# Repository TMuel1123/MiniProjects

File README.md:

MiniProjects
============

This repository contains various mini projects where it would be to much to make a own repository for each project.

ATtiny85Minimal
-------------------------

This board was just a test of the order peocedure at OSH Park. It is a simple board which contains an ATtiny85 a button and a LED.

<pre>
// ATMEL ATTINY45 / ARDUINO
//
//                          +-\/-+
// (Reset) Ain0 (D 5) PB5  1|    |8  Vcc
//         Ain3 (D 3) PB3  2|    |7  PB2 (D 2) Ain1 (SCK)
//         Ain2 (D 4) PB4  3|    |6  PB1 (D 1) pwm1 (MISO)
//                    GND  4|    |5  PB0 (D 0) pwm0 (MOSI) INT0
//                          +----+
</pre>

* Bread board friendly
* Push button is connected to D0 which is INT0
* Has a LED connected to D1 which is a PWM output
* The gerber files in the zip file ./ATtiny85Minimal/Gerber+brd/ATtiny85Minimal.zip can be directly uploaded to OSHPark.com to order it.

MegaMiniProto
-------------------------

This is a shield for the last third of the Arduino Mega2560.

* It covers the pins 14-53 and A8-A15. These pins include USART 1-3 (14-19), I2C (20,21), PWM (44-46) and SPI (50-53).
* It still fits onto the Arduino Mega2560 if a normal shield ia connected to the Arduino Mega.
* The gerber files in the zip file ./Gerber+brd/MegaMiniProto.zip can be directly uploaded to OSHPark.com to order it.

3x_74HC595
-------------------------

This board contains three 74HC595 shift registers

* Bread board friendly
* the boards can be chained together
* The gerber files in the zip file ./3x_74HC595/Gerbers/3x_74HC595.zip can be directly uploaded to OSHPark.com to order it.

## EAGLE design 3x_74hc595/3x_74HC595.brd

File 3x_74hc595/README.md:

3x 74HC595
============

This board contains three 74HC595 shift registers

* Bread board friendly
* the boards can be chained together
* The gerber files in the zip file ./3x_74HC595/Gerbers/3x_74HC595.zip can be directly uploaded to OSHPark.com to order it.

Revision 1.1
------------
* Rounded edges of the board outline
* Added labels for the IO

Revision 1.2
------------
* Moved the OUT connector for better daisy chaining

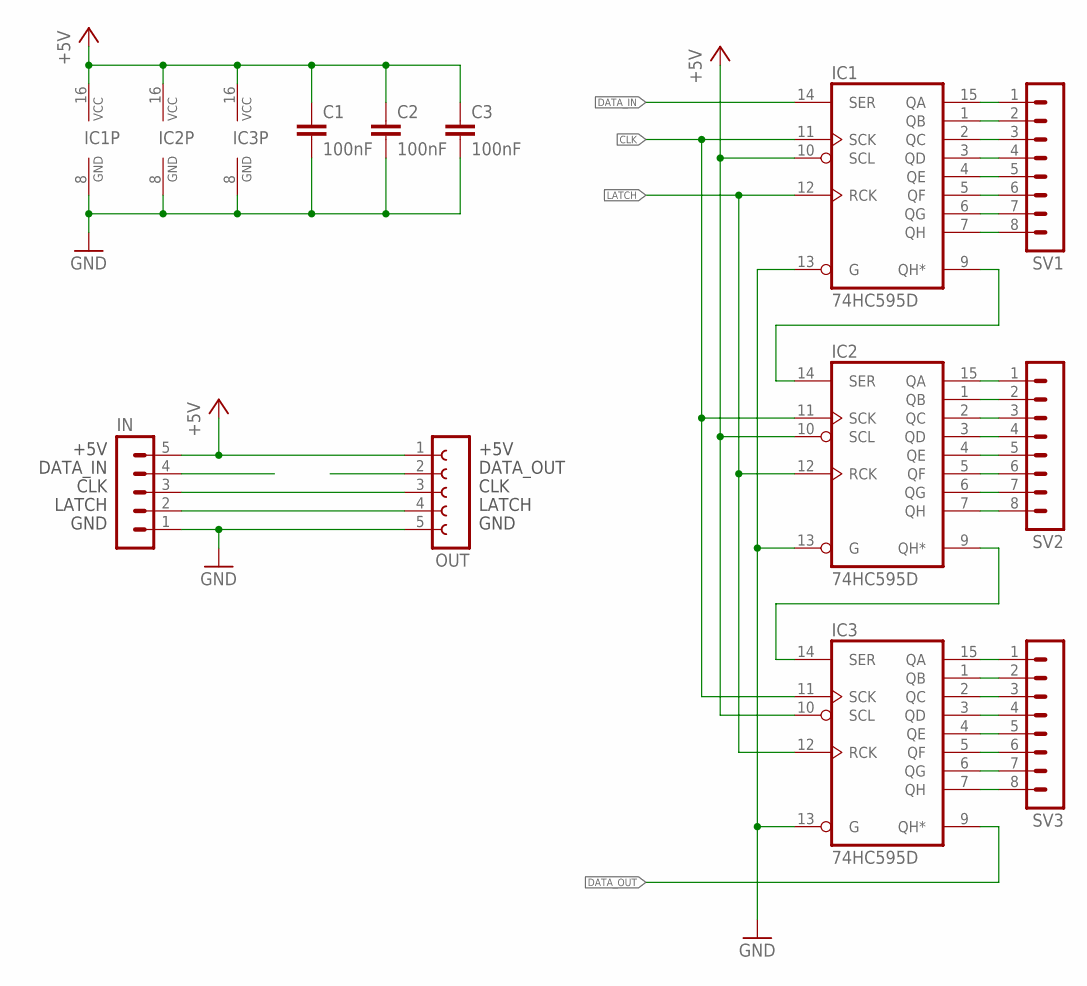
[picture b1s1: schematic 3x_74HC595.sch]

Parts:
C1, C2, C3: 100nF; C1206
IC1, IC2, IC3: 74HC595D; SO16
IN: MA05-1W
OUT: FE05W
SV1, SV2, SV3: MA08-1W

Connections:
1QA: IC1.15 (QA), SV1.1
1QB: IC1.1 (QB), SV1.2
1QC: IC1.2 (QC), SV1.3
1QD: IC1.3 (QD), SV1.4
1QE: IC1.4 (QE), SV1.5
1QF: IC1.5 (QF), SV1.6
1QG: IC1.6 (QG), SV1.7
1QH: IC1.7 (QH), SV1.8
1SHIFTOUT: IC1.9 (QH*), IC2.14 (SER)
2QA: IC2.15 (QA), SV2.1
2QB: IC2.1 (QB), SV2.2
2QC: IC2.2 (QC), SV2.3
2QD: IC2.3 (QD), SV2.4
2QE: IC2.4 (QE), SV2.5
2QF: IC2.5 (QF), SV2.6
2QG: IC2.6 (QG), SV2.7
2QH: IC2.7 (QH), SV2.8
2SHIFTOUT: IC2.9 (QH*), IC3.14 (SER)
3QA: IC3.15 (QA), SV3.1
3QB: IC3.1 (QB), SV3.2
3QC: IC3.2 (QC), SV3.3
3QD: IC3.3 (QD), SV3.4
3QE: IC3.4 (QE), SV3.5
3QF: IC3.5 (QF), SV3.6
3QG: IC3.6 (QG), SV3.7
3QH: IC3.7 (QH), SV3.8
+5V: C1.1, C2.1, C3.1, IC1.10 (SCL), IC1.16 (VCC), IC2.10 (SCL), IC2.16 (VCC), IC3.10 (SCL), IC3.16 (VCC), IN.5, OUT.1
CLK: IC1.11 (SCK), IC2.11 (SCK), IC3.11 (SCK), IN.3, OUT.3
DATA_IN: IC1.14 (SER), IN.4
DATA_OUT: IC3.9 (QH*), OUT.2
GND: C1.2, C2.2, C3.2, IC1.8 (GND), IC1.13 (G), IC2.8 (GND), IC2.13 (G), IC3.8 (GND), IC3.13 (G), IN.1, OUT.5
LATCH: IC1.12 (RCK), IC2.12 (RCK), IC3.12 (RCK), IN.2, OUT.4

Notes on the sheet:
+5V
DATA_IN
CLK
LATCH
GND
DATA_OUT

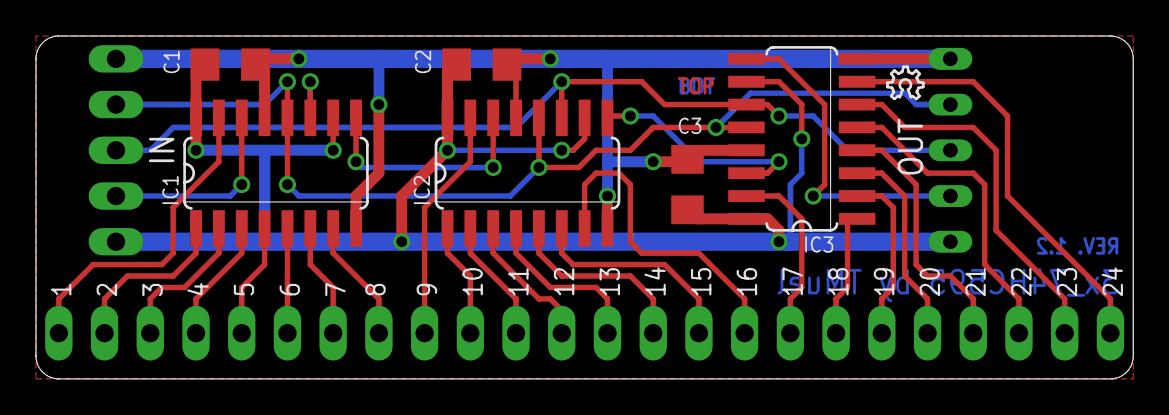
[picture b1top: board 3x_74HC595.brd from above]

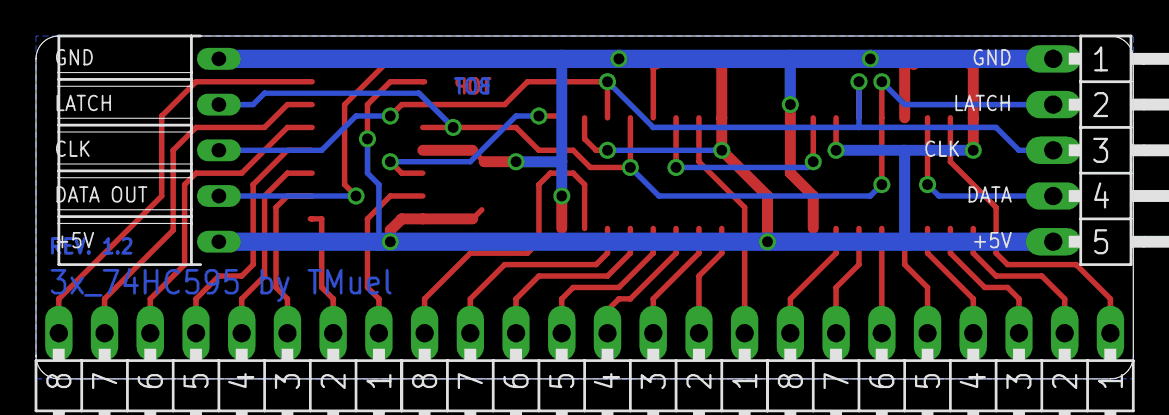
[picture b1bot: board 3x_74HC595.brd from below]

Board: 2 copper layers, 61.0 x 19.1 mm, 12 parts (5 on the bottom side), 32 nets.

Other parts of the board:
U$1: OSHW_6X70_NOTEXT

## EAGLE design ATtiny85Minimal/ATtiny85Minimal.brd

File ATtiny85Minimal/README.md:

ATtiny85Minimal
============

This board was just a test of the order peocedure at OSH Park. It is a simple board which contains an ATtiny85 a button and a LED.

<pre>
// ATMEL ATTINY45 / ARDUINO
//
//                          +-\/-+
// (Reset) Ain0 (D 5) PB5  1|    |8  Vcc
//         Ain3 (D 3) PB3  2|    |7  PB2 (D 2) Ain1 (SCK)
//         Ain2 (D 4) PB4  3|    |6  PB1 (D 1) pwm1 (MISO)
//                    GND  4|    |5  PB0 (D 0) pwm0 (MOSI) INT0
//                          +----+
</pre>

* Bread board friendly
* Push button is connected to D0 which is INT0
* Has a LED connected to D1 which is a PWM output
* The gerber files in the zip file ./ATtiny85Minimal/Gerber+brd_REV_1.0/ATtiny85Minimal.zip can be directly uploaded to OSHPark.com to order it.

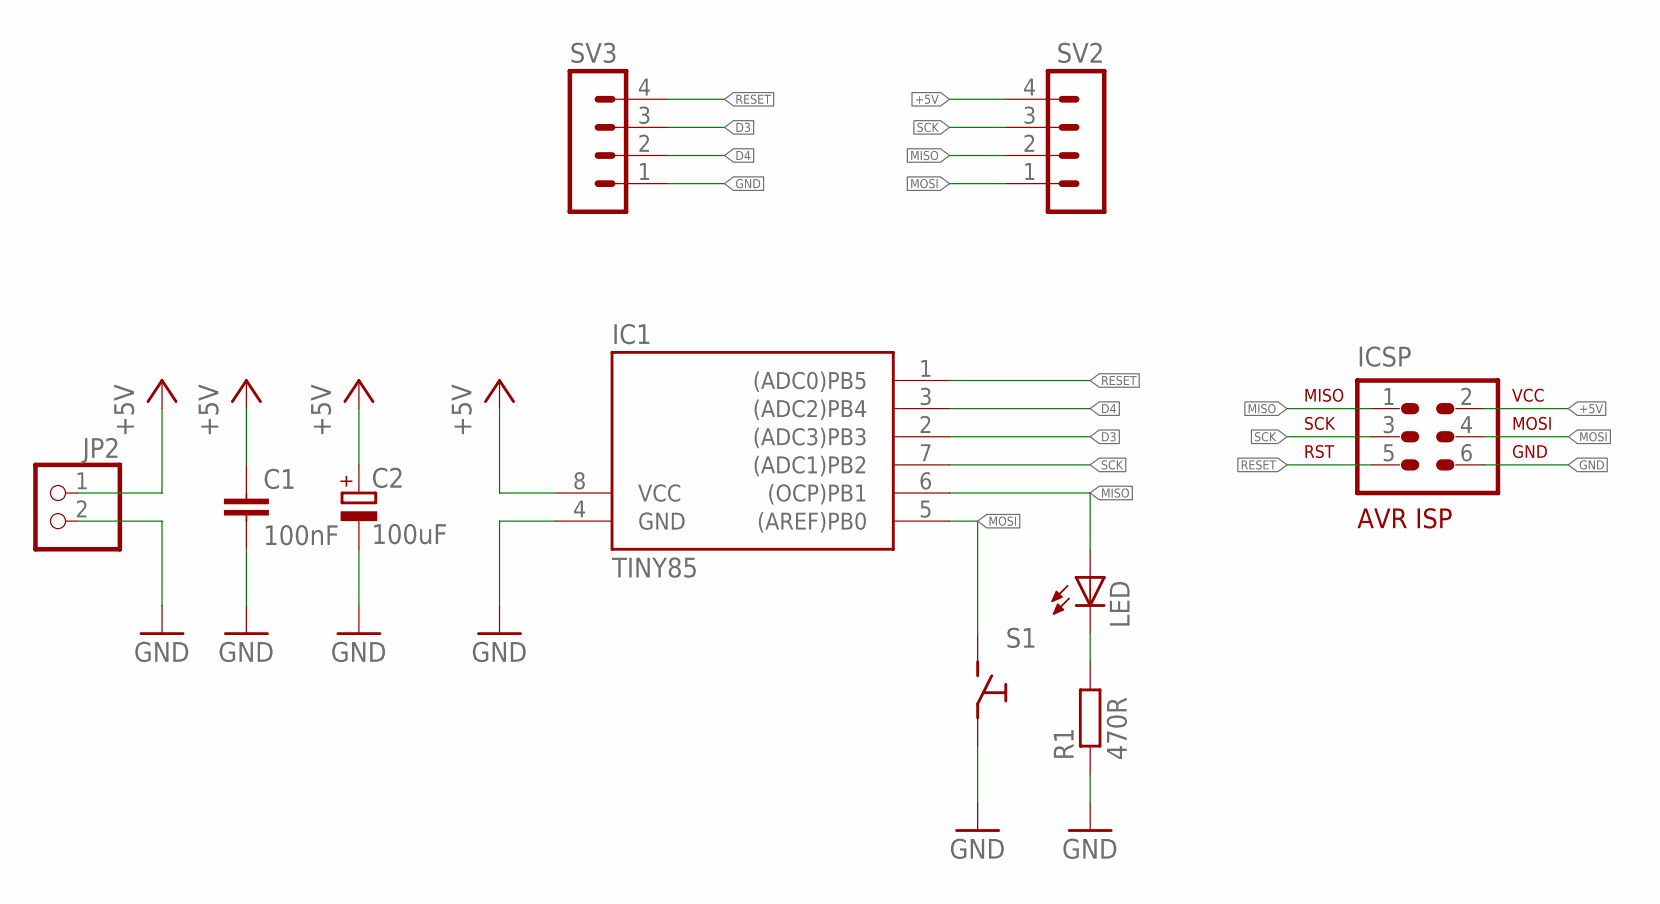
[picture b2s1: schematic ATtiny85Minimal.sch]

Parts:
C1: 100nF; C025-030X050
C2: 100uF; E2-5
IC1: TINY85; DIL08
ICSP: AVR-ISP-6VERT; AVR-ISP-6
JP2: PINHD-1X2; 1X02
LED: LED3MM
R1: 470R; 0207/7
S1: TASTER; MICROSCHALTER
SV2, SV3: MA04-1

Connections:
+5V: C1.1, C2.+, IC1.8 (VCC), ICSP.2, JP2.1, SV2.4
D3: IC1.2 ((ADC3)PB3), SV3.3
D4: IC1.3 ((ADC2)PB4), SV3.2
GND: C1.2, C2.-, IC1.4 (GND), ICSP.6, JP2.2, R1.1, S1.P$2, SV3.1
MISO: IC1.6 ((OCP)PB1), ICSP.1, LED.A, SV2.2
MOSI: IC1.5 ((AREF)PB0), ICSP.4, S1.P$1, SV2.1
unnamed: LED.K (C), R1.2
RESET: IC1.1 ((ADC0)PB5), ICSP.5, SV3.4
SCK: IC1.7 ((ADC1)PB2), ICSP.3, SV2.3

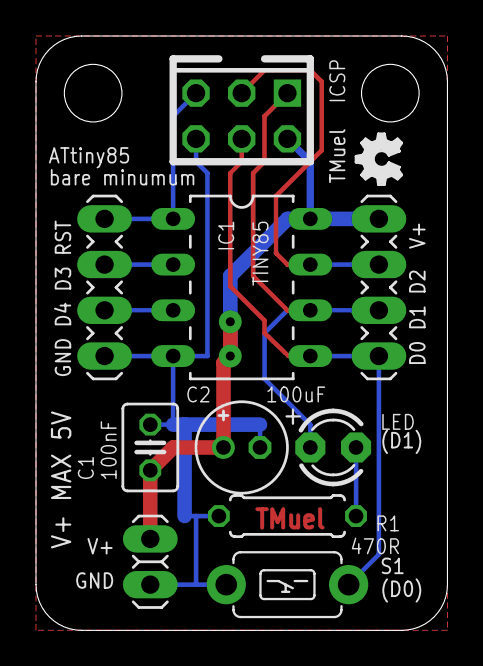
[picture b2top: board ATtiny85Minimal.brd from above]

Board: 2 copper layers, 22.9 x 33.0 mm, 11 parts (0 on the bottom side), 9 nets.

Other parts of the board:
U$6: OSHW_FILLX100_NOTEXT

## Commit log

2013-11-27 Added The MegaMiniProto shield for the Arduino Mega2560
2013-11-27 Added OSH Park info
2013-11-27 Added README.md to the MegaMiniProto project
2013-11-27 Added the ATtiny85Minimal Project
2013-12-11 * Removed revision number from the Gerber+brd folder * Made the text more bold on the top and bottom silk screen. Now it has the eagle setting size 32mil ratio 12%. The ratio of 12% seems to be the m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
2013-12-11 * Made the text more bold on the top and bottom silk screen. Now it has the eagle setting size 32mil ratio 12%. The ratio of 12% seems to be the minimum that can be cleanly printed
2013-12-11 Update README.md
    Minor change in the links to the gerber files
2013-12-11 Moved Gerber folder
2013-12-20 Fixed a horrible mistake. The holes of all vias on the board where 0.8mm so that pinheaders do not fit through the holes. I've enlarged the drills of the vias for the connection to the Arduino to 1.2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
2013-12-20 Minor change in bottom silk screen
2014-09-14 Added 3x_74HC595 Board with three shift registers
2014-09-14 Added the zip file with the 3x_74HC595 gerbers
2014-09-14 Fixed bottom silk screen of MegaMiniProto
2014-09-14 Added image and README.md for the 3x_74HC595 board
2014-09-14 3x_74HC595 Revision 1.1 ------------ * Rounded edges of the board outline * Added labels for the IO
2014-10-10 Moved the OUT connector for better daisy chaining
